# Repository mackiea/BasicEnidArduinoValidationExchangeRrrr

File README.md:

# BasicEnidArduinoValidationExchangeRrrr
An interface from the [NABU](https://nabu.ca/) via [ENID](https://github.com/mackiea/ExternalNabuInterfaceDevice) to the [Adafruit Boarduino](https://www.gravitech.us/usbboacokitv.html).

# Why interface an Arduino to a NABU?
* Debugging using a serial interface. During graphical operations, it's not easy or desirable to spit out the value of the variable asdf123wtf onto the TV screen.
* Nailing down how the NABU's Option Card protocol works. The documentation I have doesn't go into detail about active lows, signal timing, and order. I want a microcontroller to read and log these signals.
* Prototyping functionality. Most of the option cards I'd like to add will probably involve a microcontroller. Arduino is as good as any!

## Why Boarduino? It's obsolete, deprecated, and old!
Because I still have a half-dozen Boarduino boards from an incomplete project from years back. I don't recommend using this unless you're in a similar situation. I will probably work on a standard ENID Arduino shield later on.
I *am* working on a Raspberry Pico interface -- [the INREPAIR](https://github.com/mackiea/InformationalNabuRemoteEnidPicoActiveInterfaceRelay).

## Bill Of Materials?
|Part|
|----|
|[Male DB-25 connector](https://www.digikey.ca/en/products/detail/adam-tech/DB25-PT-1/9832353?so=80268516&content=productdetail_CA&mkt_tok=MDI4LVNYSy01MDcAAAGKN8fie8Y-7Hh2L_QOUR0o5PEybW02wXRuSnJHNaHE-498B2KL8l0akRq-CO76D-x000gPta5qhzrv-7rck9JXzVGoOTc-avJm5PfcgFbQ)|
|2.54mm male & female headers|
|Boarduino|
|Banana|

Eat the banana, rethink your life choices, then slap this together!

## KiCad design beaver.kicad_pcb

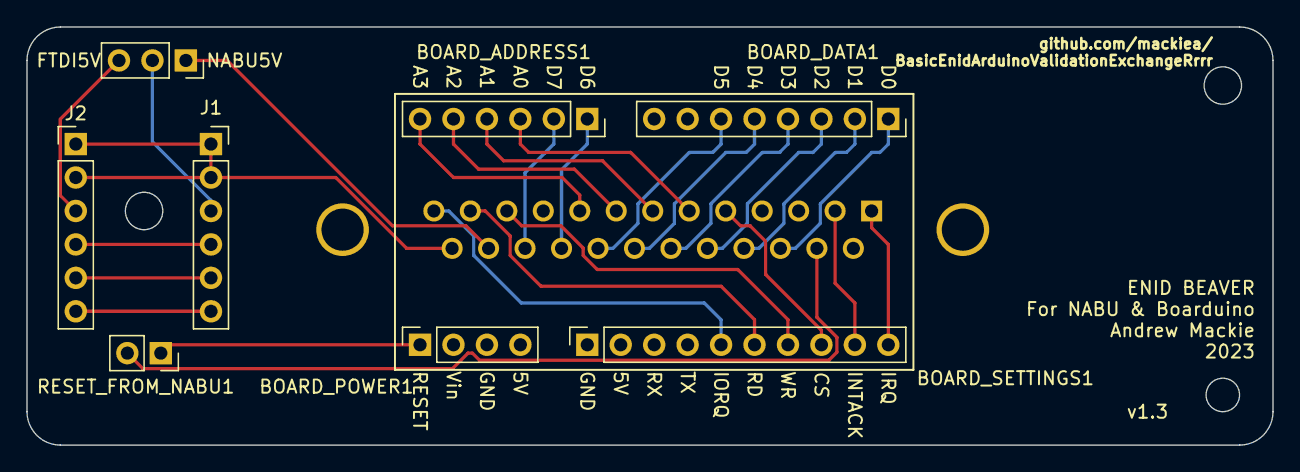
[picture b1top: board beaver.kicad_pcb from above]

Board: 2 copper layers, 94.6 x 31.8 mm, 9 parts (1 on the bottom side), 27 nets.

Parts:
BOARD_ADDRESS1: Conn_01x06_Female; PinSocket_1x06_P2.54mm_Vertical
BOARD_DATA1: Conn_01x08_Female; PinSocket_1x08_P2.54mm_Vertical
BOARD_POWER1: Conn_01x04_Female; PinSocket_1x04_P2.54mm_Vertical
BOARD_SETTINGS1: Conn_01x10_Female; PinSocket_1x10_P2.54mm_Vertical
ENID1: DB25_Male_MountingHoles; DSUB-25_Male_Vertical_P2.77x2.84mm_MountingHoles
J1: BOARD_FTDI; PinSocket_1x06_P2.54mm_Vertical
J2: FTDI; PinHeader_1x06_P2.54mm_Vertical
POWER_FROM_ENID_OR_FTDI1: Conn_01x03_Male; PinSocket_1x03_P2.54mm_Vertical
RESET_FROM_NABU1: Conn_01x02_Male; PinSocket_1x02_P2.54mm_Vertical

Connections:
+5V_1: ENID1.24, POWER_FROM_ENID_OR_FTDI1.1
ADDRESS_0: BOARD_ADDRESS1.3, ENID1.6
ADDRESS_1: BOARD_ADDRESS1.4, ENID1.7
ADDRESS_2: BOARD_ADDRESS1.5, ENID1.8
ADDRESS_3: BOARD_ADDRESS1.6, ENID1.9
BOARD_RESET: BOARD_POWER1.1, RESET_FROM_NABU1.1
CARD_SELECT: BOARD_SETTINGS1.8, ENID1.5
DATA_0: BOARD_DATA1.1, ENID1.16
DATA_1: BOARD_DATA1.2, ENID1.17
DATA_2: BOARD_DATA1.3, ENID1.18
DATA_3: BOARD_DATA1.4, ENID1.19
DATA_4: BOARD_DATA1.5, ENID1.20
DATA_5: BOARD_DATA1.6, ENID1.21
DATA_6: BOARD_ADDRESS1.1, ENID1.22
DATA_7: BOARD_ADDRESS1.2, ENID1.23
GROUND_1: ENID1.25, J1.1, J1.2, J2.1, J2.2
INTERRUPT_ACKNOWLEDGE: BOARD_SETTINGS1.9, ENID1.2
INTERRUPT_REQUEST: BOARD_SETTINGS1.10, ENID1.1
IO_REQUEST: BOARD_SETTINGS1.5, ENID1.13
unnamed: J1.3, POWER_FROM_ENID_OR_FTDI1.2
unnamed: J1.4, J2.4
unnamed: J1.5, J2.5
unnamed: J1.6, J2.6
unnamed: J2.3, POWER_FROM_ENID_OR_FTDI1.3
READ: BOARD_SETTINGS1.6, ENID1.12
RESET: ENID1.15, RESET_FROM_NABU1.2
WRITE: BOARD_SETTINGS1.7, ENID1.11

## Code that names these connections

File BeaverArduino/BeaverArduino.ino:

enum Nabu_pins {
  IO_REQUEST = 2,
  READ = 3,
  WRITE = 4,
  CARD_SELECT = 5,
  INTERRUPT_ACKNOWLEDGE = 6,
  WAIT_REQUEST=7,
  INTERRUPT_REQUEST = 8,

  EXTRA_2 = 9,

  DATA_0 = 10,
  DATA_1 = 11,
  DATA_2 = 12,
  DATA_3 = 13,
  DATA_4 = 14,
  DATA_5 = 15,
  DATA_6 = 16,
  DATA_7 = 17,

  ADDRESS_0 = 18,
  ADDRESS_1 = 19,
  ADDRESS_2 = 20,
  ADDRESS_3 = 21,

  EXTRA_1 = 22,
  EXTRA_0 = 23,

  SIZE = 24
};

#define DATA_PINS PINB

String pinName[SIZE] = {
  "IO_RD",
  "IO_WR"

  "IO_RQ",
  "RD",
  "WR",
  "CARD",
  "INT_ACK",
  "WAIT_RQ",
  "INT_RQ",

  "E2",

  "D0",
  "D1",
  "D2",
  "D3",
  "D4",
  "D5",
  "D6",
  "D7",

  "A0",
  "A1",
  "A2",
  "A3",

  "E1",
  "E0"
  };
boolean pinState[SIZE];

void reportState(String summary) {
  for (int pin = IO_REQUEST; pin < SIZE; pin++) {
    if(EXTRA_0 == pin || EXTRA_1 == pin || EXTRA_2 == pin) {
      continue; // Don't sense the floaty, unused pins.
    }
    Serial.print(pinState[pin] ? "1" : "0");
    if(INTERRUPT_REQUEST == pin) {
      Serial.print(" ");
    } else if(DATA_7 == pin) {
      Serial.print("(");
      Serial.print(String(DATA_PINS, HEX));
      Serial.print(") ");
    }
  }
  Serial.print(summary);
  Serial.println();
}

void setup() {
  Serial.begin(9600);
  while (!Serial) {
    delay(100);
  }

  Serial.println();
  Serial.println("Basic ENID Arduino Validation ExchangeRrr");
  Serial.println("-----------------------------------------");
  Serial.println("IRWCIWI     Data    Addr");
  Serial.println("RDRSARR 01234567Hex 0123");
  Serial.println("------- ----------- ----");

  for (int pin = IO_REQUEST; pin < SIZE; pin++) {
    pinMode(pin, INPUT);
    pinState[pin] = digitalRead(pin);
  }

  reportState("");
}

void loop() {
  String summary = "";
  boolean changed = false;
  for (int pin = IO_REQUEST; pin <= ADDRESS_3; pin++) {
    if(EXTRA_0 == pin || EXTRA_1 == pin || EXTRA_2 == pin) {
      continue; // Don't sense the floaty, unused pins.
    }
    boolean oldState = pinState[pin];
    pinState[pin] = digitalRead(pin);
    if(pinState[pin] != oldState) {
      changed = true;
      summary.concat(pinState[pin] ? " +" : " -");
      summary.concat(pinName[pin]);
    }
  }
  if(changed) {
    reportState(summary);
  }
}

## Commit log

2023-03-07 Added Kicad files.
2023-03-07 Added images.
2023-03-23 Added pics of printed boards
2023-04-07 Boarduino pinout was wrong for 4 pins. Will need to drop support for WAIT_REQUEST.
2023-04-07 Updated for Boarduino pinfix.
2023-04-07 Added first Arduino code.
2023-04-12 Added license.
2023-04-15 Corrected ENID's DB-25 orientation.
